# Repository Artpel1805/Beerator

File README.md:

# <div align="center">Beerator</div>
## Introduction

Le but du projet est de réaliser intégralement un robot capable de se déplacer, de chercher et d’attraper une canette (de bière ? 😶), relever sa couleur, puis de la déposer dans la zone de couleur correspondante.
Partant d’une liste de tous les composants principaux à employer et d’une proposition de châssis, toutes les étapes sont à réaliser de l’aspect matériel (Modélisation sous logiciel de CAO, soudage des composants) jusqu’à l’asservissement logiciel, en passant par la planification et la réalisation du PCB.

Voici un model 3D de ce à quoi pourrais ressembler le robot:

Le travail fut réparti entre les quatre membres de l’équipe, et les responsabilités suivantes furent attribuées:
* Chef de projet / Responsable intégration : Arthur Pellegrin
* Responsable Software : Nassim Rami
* Responsable Hardware : Adrien Lenoir
* Responsable Livrables : Clarisse Cheng

À l’écriture de ses lignes, nous avons planifié tout le projet, réalisé le PCB, designé et imprimé le châssis. Les composants sont en cours de soudage. Il reste ainsi à réaliser l’assemblage des pièces, l’algorithme de fonctionnement du robot, la commande des différents actionneurs, les calculs d’odométrie, et l’asservissement logiciel.

## General Informations

Vous trouverez dans ce repo bon nombre de dossier.

- Nous avons dans un premier temps rassembler les contraintes et les fonctionnalités du robot dans un cahier des charges: [Cahier des Charges](Cahier%20des%20Charges)

- Nous avons ensuite listé toutes les documentations des composants que nous utiliserons pour répondre à notre cahier des charges dans le dossier [Documentation](Documentation)

- Après cela nous avons architecturer la partie électronique du projet dans le dossier [Diagramme](Diagramme)

- Une fois l'architecture satisfaisante nous avons modéliser la carte électronique sous KiCaD vous trouverez le projet dans le dossier [KiCad/Beerator](KiCad/Beerator). Vous pourrez aussi trouver la BOM dans le fichier

- Nous avons en parallele esssayé d'améliorer le modele 3D du robot. Des choix ont été fait afin d'amméliorer la répartition des masses dans le robots et avoir une meilleure disposition des capteurs.

Les différents travaux effectués sont détaillés dans les parties qui suivent.

## Architecture du projet, schémas fonctionnels

### Architecture de la carte

Pour notre robot, nous proposons l'architecture suivante pour la carte:

Et pour les capteurs:

* Les deux capteurs IR serviront à détecter les bordures, l’un sera placé à l’avant gauche du robot tandis que l’autre sera à l’avant droit. Ceci évitera au robot de tomber lorsque la distance entre la table et le robot sera supérieur à 5-10 cm environ. Ces deux capteurs IR sont respectivement connectés à une PIN de la STM32, un PIN ADC permettant de recueillir la distance à laquelle se situe la bordure. Le tout étant relié à un régulateur 3.3V permettant de contrôler l’intensité du courant et la tension de sortie.

* Le capteur TOF est connecté à 4 PIN du STM32 avec 2 connexions I2C, 1 EXTI et 1 GPIO OUT. Celui-ci nous permet de connaître la distance à laquelle se situent les canettes.

* Le capteur de couleur est équipé d'un oscillateur interne, oscillateur qui produit une onde carrée dont la fréquence est proportionnelle à l'intensité de la couleur. Fréquence qui nous permettra de déterminer la couleur de la canette. Ce capteur de couleur a une portée très, c’est pour cela que nous l’avons placer au creu de la pince.

* Quatre PWM seront utilisés pour contrôler le hacheur droit et gauche des moteurs

### Architecture de l’alimentation

Voici l’architecture de l’alimentation:

Dans un premier temps, la batterie de 7.2V va nous permettre d’alimenter nos différents régulateurs qui vont à leur tour alimenter les composants de notre robot.

Les capteurs TOF et IR ont besoin d’une tension de maximale de 2.8V, on utilise donc un régulateur 3.3V pour abaisser la tension de l’alimentation. 
De même, pour le capteur de couleur, nous utilisons un régulateur 5V.

### Diagramme d’état

Voici le diagramme d’état du robot qui spécifie les réactions du robots à différents évènements qui pourraient avoir lieu. Le but du robot est d'abord de détecter la canette ou les canettes présente sur la table, pour se diriger vers elle, la saisir puis la déposer dans la zone qui correspond à sa couleur. Ces étapes sont développées dans le diagramme d’état ci-contre.

## Planification du circuit, Création du PCB

Comme vu précédemment nous avons découpé l'électronique de notre robot en 4 blocs fonctionnels.

Nous devons maintenant créer le schéma électronique de notre carte en respectant cette répartition. Cela n’a pas d'effet sur l'électronique impliqué, mais cela aidera à la maintenabilité et à la lisibilité du projet.

De même, nous traitons chaque composant indépendamment. Ils seront reliés grâce à des labels dans le logiciel * KiCad *.

### ALIMENTATION

Nous avons décidé de connecter la batterie grâce à un JST, ainsi nous pourrons facilement la retirer pour la recharger.
Concernant les régulateurs, nous dimensionnons leurs capacités de découplage en accord avec leurs documentations respectives.

Nous avons ensuite décidé de rajouter des témoins d’alimentation sur la batterie et le 3.3V. Les leds que nous avons choisies consomment 10mA pour fournir une luminosité maximale.
Comme ce sont uniquement des témoins (Nous n’avons pas besoin de beaucoup de luminosité) et que le 3.3V ne peut pas fournir une trop grande intensité nous avons choisis de réduire le courant maximal à 1mA. 
Nous dimensionnons donc les résistances en conséquence, avec une loi d’ohm sachant que les LEDs sont en 3V. 

### CAPTEURS

Nous avons décidé de connecter tous nos capteurs grâce à des JST. 
Cela permettra une meilleure modularité physique des capteurs sur le robot.
Cela évite aussi de concevoir une grande carte ou plusieurs cartes, les capteurs disposant presque tous de leur propre carte.

Nous avons quand même dû ici respecter la géométrie des capteurs afin que les JST correspondent aux bonnes I/O des cartes électroniques des capteurs.

Des résistances de Pull-Up ont dû être ajoutées, pour l’I2C car cela est nécessaire pour que ce protocole fonctionne correctement.

### ACTIONNEURS

Nous avons 3 actionneurs - 2 MCC et 1 Servomoteur.

Les MCC sont commandés par des Drivers et leurs capacités de découplage.
Cette partie du projet est assez délicate. Nous décidons donc de mettre des Solder Jump afin de pouvoir tester nos signaux avant de les connecter aux moteurs.

Le Servo quant à lui suit un protocole particulier, il sera branché sur un port USART en mode Half-Duplex du uP nécessitant une résistance de Pull-Up.

### CONTRÔLEUR

Jusqu’ici tous les modèles électroniques et les placements de toutes les I/O étaient imposés par les constructeurs.

Nous modélisons le microcontrôleur avec ses 64 broches. 
Ensuite nous avons dû brancher tous nos composants à notre microcontrôleur.

Nous avons mis un point d’honneur à optimiser le choix des broches en suivant un protocole bien particulier: 
Regrouper au maximum les broches étant reliées à un même composant
Organiser les broches de manière à minimiser les croisements lors du routage
Segmenter les sous-circuits
Prendre en compte les problèmes de compatibilité électgromagnétique

Grâce au logiciel STM32CubeMx nous avons pu placer les broches sur des pins répondant aux besoins.

Nous devons aussi alimenter le STM32 et il ne faut surtout pas oublier les capacités de découplage car l’alimentation doit être la plus stable possible.

Nous choisissons aussi de rajouter un Quartz externe, car l’horloge est plus précise.

Il ne faut pas oublier de rajouter, les branchements pour le STLink car c’est lui qui nous permettra de programmer le STM32.

Enfin nous réalisons une analyse électrique de notre circuit pour savoir s’il comporte des erreurs et nous les corrigeons jusqu’à ce qu’il n’y en ai plus.

### Production du PCB

La prochaine étape est d’assigner les empreintes correspondants aux composants. Nous utiliserons des composants SMD 0603. Pour les connecteurs nous avons utilisé des connecteurs JST de type JST HX 2.54mm.
On peut remarquer que certains composants ne sont pas assignés, en effet ce sont les composants qui seront directement soudé au capteur donc ils ne doivent pas être présent sur notre PCB

Nous travaillons sur un PCB 4 couches, on décide donc d’y placer 2 plans de potentiels séparés par 2 plans de masses pour d'obscures raisons de CEM.
On peut voir ci dessous le Stack-Up de notre carte

* <font color=red>5V (Rouge)</font>
* <font color=green>GND (Vert)</font>
* <font color=yellow>3,3V (Jaune)</font>
* <font color=blue>GND (Bleu)</font>

JLC PCB, le fabricant de nos carte nous impose aussi des contraintes de conception que nous devons renseigner.

La prochaine est le placement des composants sur le PCB.
Nous essayons de regrouper les composants au maximum par groupe pour que le routage soit le plus simple possible

On décide aussi de placer le STM32 au centre car c’est lui qui possède le plus de connexion.

On voit ci dessous en vert tous les composants relatif au contrôle, en rouge tous le bloc actionneurs, en bleu le bloc alimentation et en jaune le bloc capteur

Nous relions ensuite tous les composants électriquement. Nous veillerons aussi à utiliser les pistes les plus larges possible surtout pour la partie puissance. 
Cela permet de laisser passer le courant nécessaire et d’éviter des problèmes de CEM.

Quelques règles de CEM que nous nous efforçons de respecter : 
Pas d’angle à 90º
Les signaux à haute fréquence ne doivent pas se croiser, et les pistes doivent être le plus court possible
Il faut essayer de respecter une distance entre les pistes

Voici ce à quoi ressemblent nos deux plans avec des pistes.

Et enfin notre carte modélisé en 3D

## Capteurs, spécificités software

Dans cette partie, on se basera sur le choix des composants et leur protocole de communication ainsi que leur fonctionnalité pour atteindre les objectifs demandés par le cahier de charge afin que le robot puisse fonctionner correctement.

### TCS3200 - Capteur de Couleur

Le capteur VEML3328 détecte les couleurs rouge, le vert, le bleu en incorporant des photodiodes, des amplificateurs et des circuits analogiques/numériques dans une seule puce CMOS. Avec ce capteur, la luminosité et la température de couleur d'un rétroéclairage d'affichage peuvent être ajusté en fonction de la source de lumière ambiante, et il peutdifférencier les environnements d'éclairage intérieurs des environnements d'éclairage extérieurs.Il existe une relation entre la sortie et l'intensité lumineuse. La gamme de  sortie est typique de 2hz à 500Khz.
Ce dispositif utilise une liaison direct avec le microcontrôleur.
Puisque le diapositif nous fournit comme output un signal variant en fréquence , on a utilisé la fonction du Timer : Input capture mode , qui permet de détecter chaque front montant et en calculant la différence on peut avoir la fréquence.

#### Calibration

Pour calibrer le capteur, nous avons besoin d'un objet blanc.On place un objet blanc près du capteur. Après le calibrage, si on garde l'objet blanc devant le capteur, on voit la valeur de 255 pour chacune des trois couleurs rouge, verte et bleue. La fonction Calibrate puis on crée une fonction Calibrate() qui  calcule et stocke les changements maximum et minimum de la fréquence de sortie du capteur dans un environnement non coloré et de couleur blanche. Ensuite,on mappe la plage de changement de couleur sur 0-255 .

Le dispositif dispose de deux broches en changeant leur état permet de choisir la couleur qu’on veut détecter en faisant appel la fonction Calibration() à chaque interruption.

Le capteur nous fournit un signal carré comme sortie variant en fréquence en fonction de la distance entre l’objet et le capteur  , c’est pour cela qu' on a utilisé la fonction Input Capture Mode du Timer qui permet de détecter chaque front montant . 
En utilisant cette fonctionnalité , on pourra calculer la fréquence en calculant la différence entre deux fronts montants et l'horloge de référence est calculée en fonction de la configuration que nous avons effectuée . puis en disant l’horloge de référence par la différence précédente.

### VL53L0X - Capteur de distance TOF

Il s'agit d'un capteur ToF (Time-of-Flight), c'est-à-dire que la distance est mesurée en mesurant le temps de vol. Le capteur vérifie combien de temps il faut à la lumière pour atteindre l'objet, rebondir dessus et revenir au capteur de réception (Réflexion). Le capteur communique avec l'hôte via l'interface I²C. Outre les broches de bus standard, une sortie d'interruption et une entrée pour l'arrêt du capteur sont également disponibles.

#### Programmation

ST ajoute une bibliothèque complète au capteur  Elle contient tout ce qui peut être fait avec le système.
On a testé la bibliothèque pour extraire les données du capteur sauf que la bibliothèque est universellement écrite et  elle prend donc beaucoup de code,ce qui représente beaucoup de mémoire Flash.
Pour cela on est obligé de créer notre propre drivers pour extraire les données et communiquer avec le capteur.

### Sharp GP2Y0D805Z0F - Capteur de Proximité Infrarouge

Ce capteur de proximité infrarouge de Pololu permet de détecter sans contact tout objet entre 0,5 et 5 cm . Sur la carte électronique,on retrouve 3 broches : la pastille carrée est la masse, la pastille du milieu est l'alimentation Vin (entre 2.7 et 6.2 V) et la dernière pastille est la sortie du capteur de proximité infrarouge.On peut améliorer la performance du capteur en plaçant une capacité (>10uF) entre l'alimentation et la masse.

## Architecture matérielle, Modélisation

### Généralités

Afin de pouvoir intégrer les éléments imposés du projet sur le robot, nous avons dû modéliser un châssis qui reprend la forme proposée en incluant les capteurs. Pour maximiser la fiabilité de ce robot en termes de trajectoire et faciliter sa commande/son asservissement, nous avons voulu modifier sa géométrie en plaçant entre autres son centre de gravité en aval de son centre de poussée (pour la marche avant), et en rendant quasi parfaitement symétrique el robot, que sa pince soit ouverte ou fermée. Ainsi les batteries se retrouvent à l’arrière, les moteurs contrôlent la rotation des roues directement à l’avant, le troisième point d'appui omni-directionnel est juste derrière les batteries, et la pince à l’opposé, tout à l’avant en porte à faux. Elle opère en un mouvement synchronisé de trois mords qui serrent et soulèvent légèrement du sol la canette interceptée, grâce à une légère inclinaison du système, comme on peut le voir ci-dessous.

Le tout confère au robot une allure de scorpion.

### Placement des capteurs

Les deux capteurs infrarouges anti-chute sont situés sur les côtés, juste devant les roues, de façon à toujours détecter la chute potentielle à temps et à pouvoir faire revenir le robot sur ses pas si nécessaire.

Le capteur de couleur est placé juste sous la pince, avec la même orientation, afin de lire au plus proche la couleur de la canette saisie, car ce type de capteur ne fonctionne pas de façon fiable au delà d’une distance de quelques centimètres.

Le capteur de distance ‘TOF’ est quant à lui placé sur un plan vertical, sur le front du robot, afin de lire sans obstruction la distance avec les obstacles/cibles rencontré(e)s.

### Dimensions des pièces

Les capteurs et actionneurs utilisés par le robot sont à l’origine de sa géométrie, et dans le souci de bâtir un modèle correspondant au mieux aux critères énoncés plus haut, il fallait à présent recenser les dimensions physiques de chaque élément. Ce recueil apparaît ci-après.

* Canette (33 cL standard) | Ø: 66 mm, H: 115 mm
* Canette (50 cL standard) | Ø: 66 mm, H: 168 mm
* Batterie (avec assez de marge pour les fils) | l: 48 mm; L: 95 mm; H: 15 mm
* Moteurs avec codeur (sans l’axe) | Ø: 25 mm, L: 59 mm
* Servomoteur (pris aux centres des points de fixation) | l: 24 mm; L: 18 mm; H: 12 mm
* Capteur IR | l: 8.9 mm; L: 21.6 mm; H: xx mm
* Capteur de couleurs | l: 28.4 mm; L: 28.4 mm; H: xx mm
* Capteur TOF | l: 12.7 mm; L: 17.8 mm; H: xx mm
* PCB (pris aux centres des points de fixation) | l: 40 mm; L: 100 mm
* Bille (Roulement omnidirectionnel) | Ø: 22.9 mm, H: 20.9 mm
* Roues avec support | Ø: 40 mm, H: 8 mm

### Cable management

Tous les câbles parcourent le chemin le plus court pour parvenir à la carte, en s'immisçant dans des sillons et fentes prévus à cet effet dans le châssis.

Ainsi on évite les erreurs de branchement, les croisement et les fils trop exposés.

### Le système de pince

Comme expliqué plus haut, la pince s’articule en trois mords synchronisés, deux maintiennent la canette, le troisième la soulève.

Le servomoteur fait passer la pince entre ses états fermés et ouverts sur une course de 90°. Deux mouvements proches mais opposés en sens ferment les deux crochets de pince arrondis, pendant que la troisième composante de la pince s’avance pour refermer l’emprise du robot sur sa bière et la soulever légèrement du sol, pour la vider pour ne pas qu’elle frotte. Cela peut paraître superflu, mais peut jouer un rôle important sur une surface non plane ou rugueuse.

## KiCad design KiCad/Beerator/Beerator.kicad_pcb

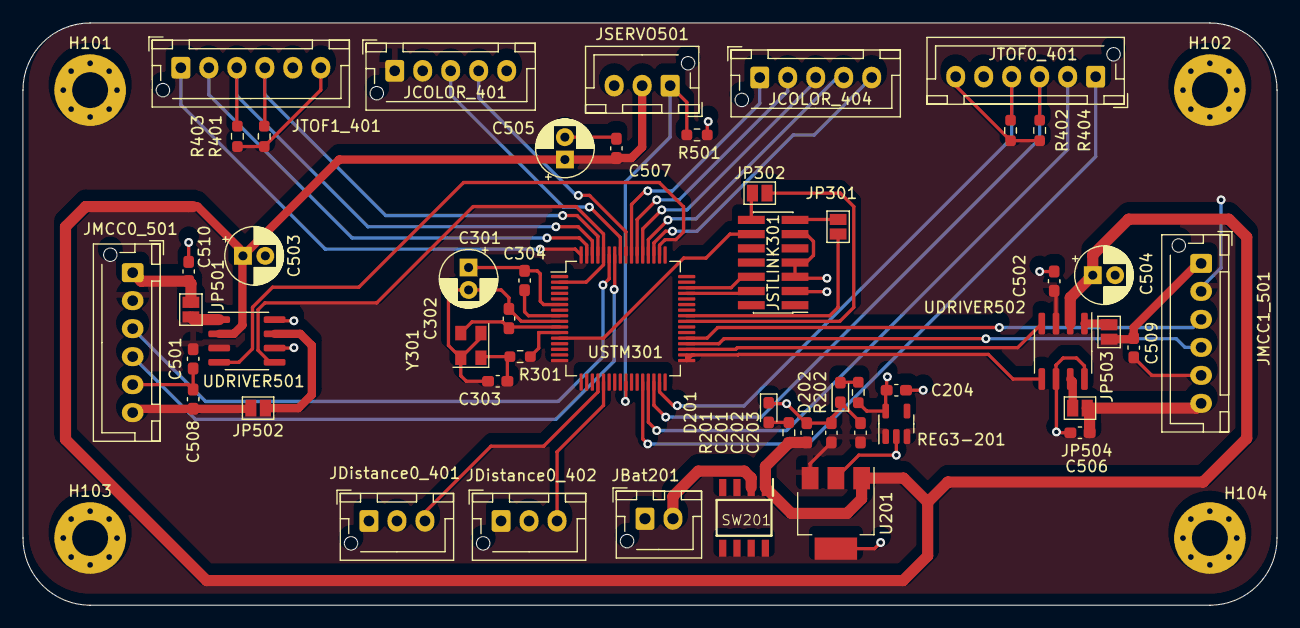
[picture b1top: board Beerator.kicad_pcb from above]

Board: 4 copper layers, 112.0 x 52.0 mm, 56 parts (0 on the bottom side), 52 nets.

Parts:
C201: 10uF; C_0603_1608Metric_Pad1.08x0.95mm_HandSolder
C202: 22uF; C_0603_1608Metric_Pad1.08x0.95mm_HandSolder
C203, C204: 1uF; C_0603_1608Metric_Pad1.08x0.95mm_HandSolder
C301: 4,7u; CP_Radial_D5.0mm_P2.00mm
C302, C303: 15p; C_0603_1608Metric_Pad1.08x0.95mm_HandSolder
C304: 100n; C_0603_1608Metric_Pad1.08x0.95mm_HandSolder
C501, C502: 1µF; C_0603_1608Metric_Pad1.08x0.95mm_HandSolder
C503, C504: 10µF; CP_Radial_D5.0mm_P2.00mm
C505: 100uF; CP_Radial_D5.0mm_P2.00mm
C506, C507, C508, C509, C510: 0.1uF; C_0603_1608Metric_Pad1.08x0.95mm_HandSolder
D201, D202: LED_Small; LED_0603_1608Metric_Pad1.05x0.95mm_HandSolder
H101, H102, H103, H104: MountingHole_Pad; MountingHole_3.2mm_M3_Pad_Via
JBat201: Conn_01x02_Female; JST_XH_B2B-XH-AM_1x02_P2.50mm_Vertical
JCOLOR_401, JCOLOR_404: Conn_01x05_Female; JST_XH_B5B-XH-AM_1x05_P2.50mm_Vertical
JDistance0_401, JDistance0_402: Conn_01x03_Female; JST_XH_B3B-XH-AM_1x03_P2.50mm_Vertical
JMCC0_501, JMCC1_501: Conn_01x06_Female; JST_XH_B6B-XH-AM_1x06_P2.50mm_Vertical
JP301, JP302, JP501, JP502, JP503, JP504: SolderJumper_2_Open; SolderJumper-2_P1.3mm_Open_Pad1.0x1.5mm
JSERVO501: Conn_01x03_Female; JST_XH_B3B-XH-AM_1x03_P2.50mm_Vertical
JSTLINK301: Conn_02x07_Odd_Even; PinHeader_2x07_P1.27mm_Vertical_SMD
JTOF0_401, JTOF1_401: Conn_01x06_Female; JST_XH_B6B-XH-AM_1x06_P2.50mm_Vertical
R201: 4,2k; R_0603_1608Metric_Pad0.98x0.95mm_HandSolder
R202: 300; R_0603_1608Metric_Pad0.98x0.95mm_HandSolder
R301: 80; R_0603_1608Metric_Pad0.98x0.95mm_HandSolder
R401, R402, R403, R404: 1k; R_0603_1608Metric_Pad0.98x0.95mm_HandSolder
R501: 10k; R_0603_1608Metric_Pad0.98x0.95mm_HandSolder
REG3-201: MCP1802x-xx02xOT; SOT-23-5
SW201: SW_DPDT_x2; NE555DR
U201: REG-5; SOT-223
UDRIVER501, UDRIVER502: ZXBM5210-S; SOIC-8_3.9x4.9mm_P1.27mm
USTM301: STM32G070RBT6; LQFP-64_10x10mm_P0.5mm
Y301: Crystal_GND23; Crystal_SMD_EuroQuartz_MT-4Pin_3.2x2.5mm

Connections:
+3.3V: C204.1, C301.1, C304.1, JDistance0_401.2, JDistance0_402.2, JSTLINK301.3, JTOF0_401.6, JTOF1_401.6, R202.1, R401.1, R402.2, R403.2, R404.1, R501.2, REG3-201.5 (VOUT), USTM301.6 (VBAT)
+5V: C202.1, C203.1, C501.2, C502.2, JCOLOR_401.1, JMCC0_501.2, JMCC1_501.2, REG3-201.1 (VIN), REG3-201.3 (~SHDN), U201.3 (OUT), UDRIVER501.3 (VDD), UDRIVER502.3 (VDD)
+BATT: C201.1, C503.1, C504.1, C505.1, C507.2, JSERVO501.2, R201.1, SW201.1 (A), U201.1 (Vin), UDRIVER501.2 (VM), UDRIVER502.2 (VM)
/Control/RX_JP: JP301.2 (B), JSTLINK301.13
/Control/TX_JP: JP302.1 (A), JSTLINK301.14
GND: C201.2, C202.2, C203.2, C204.2, C301.2, C302.2, C303.1, C501.1, C502.1, C503.2, C504.2, C505.2, C506.1, C507.1, C508.1, C509.1, C510.1, D201.1 (K), D202.1 (K), H101.1, H102.1, H103.1, H104.1, JBat201.1, JCOLOR_401.2, JCOLOR_401.5, JDistance0_401.1, JDistance0_402.1, JMCC0_501.5, JMCC1_501.5, JSERVO501.3, JSTLINK301.5, JSTLINK301.7, JSTLINK301.11, JTOF0_401.5, JTOF1_401.5, REG3-201.2 (GND), U201.2 (GND), U201.4 (GND), UDRIVER501.6 (VREF), UDRIVER501.8 (GND), UDRIVER502.6 (VREF), UDRIVER502.8 (GND), USTM301.9 (VSS/VSSA), Y301.2, Y301.4
IR1-OUT: JDistance0_402.3, USTM301.21 (PA4/GPIO_EXTI4)
IR2-OUT: JDistance0_401.3, USTM301.20 (PA3/GPIO_EXTI3)
NPWM_D1: UDRIVER501.5 (REV), USTM301.2 (PC12/TIM14_CH1/PWM), USTM301.60 (PB6/PWM/TIM16_CH1N)
NPWM_D2: UDRIVER502.5 (REV), USTM301.33 (PB13/TIM15_CH1N/PWM), USTM301.34 (PB14/TIM15_CH1/PWM)
NRST: JSTLINK301.12, USTM301.12 (NRST)
unnamed: C302.1, USTM301.10 (PF0-OSC_IN), Y301.3
unnamed: C303.2, R301.1, Y301.1
unnamed: C304.2, USTM301.8 (VDD/VDDA)
unnamed: D201.2 (A), R201.2
unnamed: D202.2 (A), R202.2
unnamed: JBat201.2, SW201.2 (B)
unnamed: JP501.1 (A), UDRIVER501.1 (OUT1)
unnamed: JP502.1 (A), UDRIVER501.7 (OUT2)
unnamed: JP503.1 (A), UDRIVER502.1 (OUT1)
unnamed: JP504.1 (A), UDRIVER502.7 (OUT2)
unnamed: R301.2, USTM301.11 (PF1-OSC_OUT)
O1_D1: C510.2, JMCC0_501.1, JP501.2 (B)
O1_D2: C509.2, JMCC1_501.1, JP503.2 (B)
O2_D1: C508.2, JMCC0_501.6, JP502.2 (B)
O2_D2: C506.2, JMCC1_501.6, JP504.2 (B)
PHASE_A_M1: JMCC0_501.4, USTM301.58 (PB4/TIM3_CH1/EncoderMode)
PHASE_A_M2: JMCC1_501.4, USTM301.36 (PA8/TIM1_CH1/EncoderMode)
PHASE_B_M1: JMCC0_501.3, USTM301.59 (PB5/TIM3_CH2/EncoderMode)
PHASE_B_M2: JMCC1_501.3, USTM301.37 (PA9/TIM1_CH2/EncoderMode)
PWM_D1: UDRIVER501.4 (FWD), USTM301.50 (PD0/TIM16_CH1/PWM)
PWM_D2: UDRIVER502.4 (FWD), USTM301.35 (PB15/TIM15_CH2/PWM)
RX: JP301.1 (A), USTM301.41 (PD9/USART3_RX)
SERVO_DATA: JSERVO501.1, R501.1, USTM301.25 (PC4/USART1_TX/Single_Wire)
SWCLK: JSTLINK301.6, USTM301.46 (PA14-BOOT0/SYS_SWCLK/)
SWDIO: JSTLINK301.4, USTM301.45 (PA13/SYS_SWDIO/)
TCS-LED: JCOLOR_401.4, USTM301.56 (PD6/GPIO_Output)
TCS-OE: JCOLOR_401.3, USTM301.57 (PB3/GPIO_Output)
TCS-OUT: JCOLOR_404.5, USTM301.51 (PD1/TIM17_CH1/Input_Capture)
TCS-S0: JCOLOR_404.1, USTM301.55 (PD5/GPIO_Outpur)
TCS-S1: JCOLOR_404.2, USTM301.54 (PD4/GPIO_Output)
TCS-S2: JCOLOR_404.3, USTM301.53 (PD3/GPIO_Output)
TCS-S3: JCOLOR_404.4, USTM301.52 (PD2/GPIO_Output)
TOF2_EXTI: JTOF1_401.1, USTM301.64 (PC10/GPIO_EXTI10)
TOF2_SCL: JTOF1_401.3, R403.1, USTM301.62 (PB8/I2C1_SCL)
TOF2_SDA: JTOF1_401.4, R401.2, USTM301.61 (PB7/I2C1_SDA)
TOF2_XSHUT: JTOF1_401.2, USTM301.63 (PB9/GPIO_OutPut)
TOF-EXTI: JTOF0_401.1, USTM301.28 (PB1/GPIO_EXTI1)
TOF-SCL: JTOF0_401.3, R404.2, USTM301.30 (PB10/I2C2_SCL)
TOF-SDA: JTOF0_401.4, R402.1, USTM301.31 (PB11/I2C2_SDA)
TOF-XSHUT: JTOF0_401.2, USTM301.29 (PB2/GPIO_OUTPUT)
TX: JP302.2 (B), USTM301.40 (PD8/USART3_TX)

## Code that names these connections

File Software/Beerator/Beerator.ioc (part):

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Mcu.Name=STM32G070RBTx
Mcu.Package=LQFP64
Mcu.UserName=STM32G070RBTx
PA11\ [PA9].GPIOParameters=GPIO_Label
PA11\ [PA9].GPIO_Label=TOF_I2C_SCL
PA11\ [PA9].Mode=I2C
PA11\ [PA9].Signal=I2C2_SCL
PA12\ [PA10].GPIOParameters=GPIO_Label
PA12\ [PA10].GPIO_Label=TOF_I2C_SDA
PA12\ [PA10].Mode=I2C
PA12\ [PA10].Signal=I2C2_SDA
PA13.Mode=Serial_Wire
PA13.Signal=SYS_SWDIO
PA14-BOOT0.Mode=Serial_Wire
PA14-BOOT0.Signal=SYS_SWCLK
PA2.GPIOParameters=GPIO_Label
PA2.GPIO_Label=TOF_INT
PA2.Signal=GPXTI2
PA3.GPIOParameters=GPIO_Label
PA3.GPIO_Label=TOF_XSHUT
PA3.Signal=GPIO_Output
PA5.GPIOParameters=GPIO_Label
PA5.GPIO_Label=TOF2_XSHUT
PA5.Signal=GPIO_Output
PB1.GPIOParameters=GPIO_Label
PB1.GPIO_Label=TCS_OUT
PB1.Signal=S_TIM14_CH1
PB10.GPIOParameters=GPIO_Label
PB10.GPIO_Label=BAT_SENSE
PB10.Mode=IN11
PB10.Signal=ADC1_IN11
PB13.GPIOParameters=GPIO_Label
PB13.GPIO_Label=TCS_S3
PB13.Signal=GPIO_Output
PB14.GPIOParameters=GPIO_Label
PB14.GPIO_Label=TCS_S2
PB14.Signal=GPIO_Output
PB15.GPIOParameters=GPIO_Label
PB15.GPIO_Label=TCS_LED
PB15.Signal=GPIO_Output
PB4.GPIOParameters=GPIO_Label
PB4.GPIO_Label=PHASE_B_M2
PB4.Signal=S_TIM3_CH1
PB5.GPIOParameters=GPIO_Label
PB5.GPIO_Label=PHASE_A_M2
PB5.Signal=S_TIM3_CH2
PB6.GPIOParameters=GPIO_Label
PB6.GPIO_Label=NPWM_M1
PB6.Mode=PWM Generation1 CH1 CH1N
PB6.Signal=TIM16_CH1N
PB7.GPIOParameters=GPIO_Label
PB7.GPIO_Label=NPWM_M2
PB7.Mode=PWM Generation1 CH1 CH1N
PB7.Signal=TIM17_CH1N
PB8.GPIOParameters=GPIO_Label
PB8.GPIO_Label=PWM_M1
PB8.Signal=S_TIM16_CH1
PB9.GPIOParameters=GPIO_Label
PB9.GPIO_Label=PWM_M2
PB9.Signal=S_TIM17_CH1
PC11.GPIOParameters=GPIO_PuPd,GPIO_Label,GPIO_ModeDefaultEXTI
PC11.GPIO_Label=IR1_OUT
PC11.GPIO_ModeDefaultEXTI=GPIO_MODE_IT_RISING
PC11.GPIO_PuPd=GPIO_NOPULL
PC11.Signal=GPXTI11
PC12.GPIOParameters=GPIO_PuPd,GPIO_Label,GPIO_ModeDefaultEXTI
PC12.GPIO_Label=IR2_OUT
PC12.GPIO_ModeDefaultEXTI=GPIO_MODE_IT_RISING
PC12.GPIO_PuPd=GPIO_NOPULL
PC12.Signal=GPXTI12
PC3.GPIOParameters=GPIO_Label
PC3.GPIO_Label=LED_GREEN
PC3.Signal=GPIO_Output
PC4.Mode=Asynchronous
PC4.Signal=USART1_TX
PC5.Mode=Asynchronous
PC5.Signal=USART1_RX
PC8.GPIOParameters=GPIO_Label
PC8.GPIO_Label=PHASE_A_M1
PC8.Signal=S_TIM1_CH1
PC9.GPIOParameters=GPIO_Label
PC9.GPIO_Label=PHASE_B_M1
PC9.Signal=S_TIM1_CH2
PD5.GPIOParameters=GPIO_Label
PD5.GPIO_Label=SERVO_DATA
PD5.Mode=Half_duplex(single_wire_mode)
PD5.Signal=USART2_TX
PF0-OSC_IN\ (PF0).Mode=HSE-External-Oscillator
PF0-OSC_IN\ (PF0).Signal=RCC_OSC_IN
PF1-OSC_OUT\ (PF1).Mode=HSE-External-Oscillator
PF1-OSC_OUT\ (PF1).Signal=RCC_OSC_OUT
RCC.HSE_VALUE=8000000
RCC.SYSCLKFreq_VALUE=64000000
RCC.SYSCLKSource=RCC_SYSCLKSOURCE_PLLCLK
board=custom

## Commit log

2022-09-21 Init + added empty index.html file
2022-09-21 Feeling index
2022-09-21 Clarisse Vibe
2022-09-21 Clarisse the Autralian
2022-09-28 Adding the Datasheets
2022-09-28 feat(Documentation): Documentation directory
2022-09-28 Diagram[TEST]
2022-09-28 Adding Batterie
2022-09-28 Quartz
2022-09-28 Mettre à jour Diagramme sans nom.drawio
2022-09-28 Driver
2022-09-28 Driver Moteur
2022-09-28 Capteur DE merde
2022-09-28 Regulateur
2022-09-28 Fixing
2022-09-28 Alimentation
2022-09-28 Input
2022-09-28 Save
2022-09-28 Regulateur 3V
2022-09-28 Lignes
2022-09-28 ServoMoteur
2022-09-28 functionnal_diagram.png
2022-09-28 feat(Diagramme + Cahier Des charges)
2022-09-28 feat(add README)
2022-09-28 Ajouté(e) Architectural_Diagram.png
2022-09-28 Ajouté(e) Diagramme sans nom.drawio.png
2022-09-29 V-cycle commitment
    Description of the steps taken in regard of the V-cycle ideology.
2022-09-29 BLOC_actuator.drawio
2022-09-29 Diagramme_BLOC.drawio
2022-09-30 BLOC_diagram.drawio
2022-10-02 Capteurs
2022-10-03 Kicad Project
2022-10-06 feat(Kicad): Schemas V1
2022-10-06 Adding the Beerator's BOM
    The BOM mainly describes the list of components to use, as well as some construction rules/specifications.
2022-10-06 Rename Beerator_BOM to Beerator_BOM.md
2022-10-06 Adding exact references to the BOM
2022-10-08 feat(KiCad): Version 2
2022-10-21 feat(last pcb version)
2022-10-21 Dimensionement Led
2022-10-21 Update_Schemas
2022-10-21 pcb_v2
2022-10-27 version_finale_pcb
2022-10-27 fichier_production
2022-11-09 Ajouté(e) Diagramme etat
2022-11-09 Mettre à jour Diagramme etat
2022-11-15 Introduction
2022-11-15 Partie Circuit et PCB, sans images
2022-11-15 Ajout illustration partie circuit et PCB
2022-11-15 Ajout illustrations circuit et PCB readme
2022-11-15 Partie Capteurs specificites software
2022-11-15 Ajout illustration capteur et aspects soft
2022-11-15 Ajout illustration readme capteurs et co
2022-11-15 Ajout partie structure matérielle, sans img
2022-11-15 Ajout illustrations partie structure materielle
2022-11-15 Ajout illustration readme partie struc physique
2022-11-15 Ajout partie architecture et diagrammes fonc
2022-11-15 Ajout illustrations architecture et diagrammes
2022-11-15 Ajout illustrations readme architec diagrammes
2022-11-15 Ajout des morceaux de codes
2022-11-16 Correction Carte
2022-11-16 CubeIDE Projet
2022-11-21 gitignore
2022-11-21 config
2022-11-21 Debut config
2022-12-01 deleting .metadata
2022-12-01 deleting .settings
2022-12-01 ADC for battery
2022-12-01 adding free Rtos
2022-12-02 Capteur FLOOR IRQ
2022-12-12 Gestion ERROR
2022-12-12 Ajout function INIT
2022-12-13 Ajout semaphore et modification fonction init
2022-12-18 Kicad Changes
2022-12-18 Beerator new tim config for motors
2022-12-23 Shell IRQ + RT
2022-12-23 XL320 RT
2022-12-31 TCS3200_F7
2023-01-09 Motor_V1
2023-01-09 Algorigramme
2023-01-10 TCS3200
2023-01-11 pid implementation
2023-01-12 odo v2
2023-01-12 fonction avance
2023-01-12 avance v2
2023-01-12 Conflict Resolution
2023-01-13 odometrie 13_01
2023-01-16 Routine recherche
2023-01-16 correction
2023-01-19 tof + os
2023-01-20 Correction Pince
2023-01-20 tcs3200-problem
